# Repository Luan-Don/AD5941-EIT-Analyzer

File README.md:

# AD5941-EIT-Analyzer
This project is based on the previous project "AD5941 Impedance Analyzer" which extends further its application in Electrical Impedance Tomography. This project focuses on making the external PCB board (containing MUX) for AD5941 Impedance Analyzer (AIA for short).

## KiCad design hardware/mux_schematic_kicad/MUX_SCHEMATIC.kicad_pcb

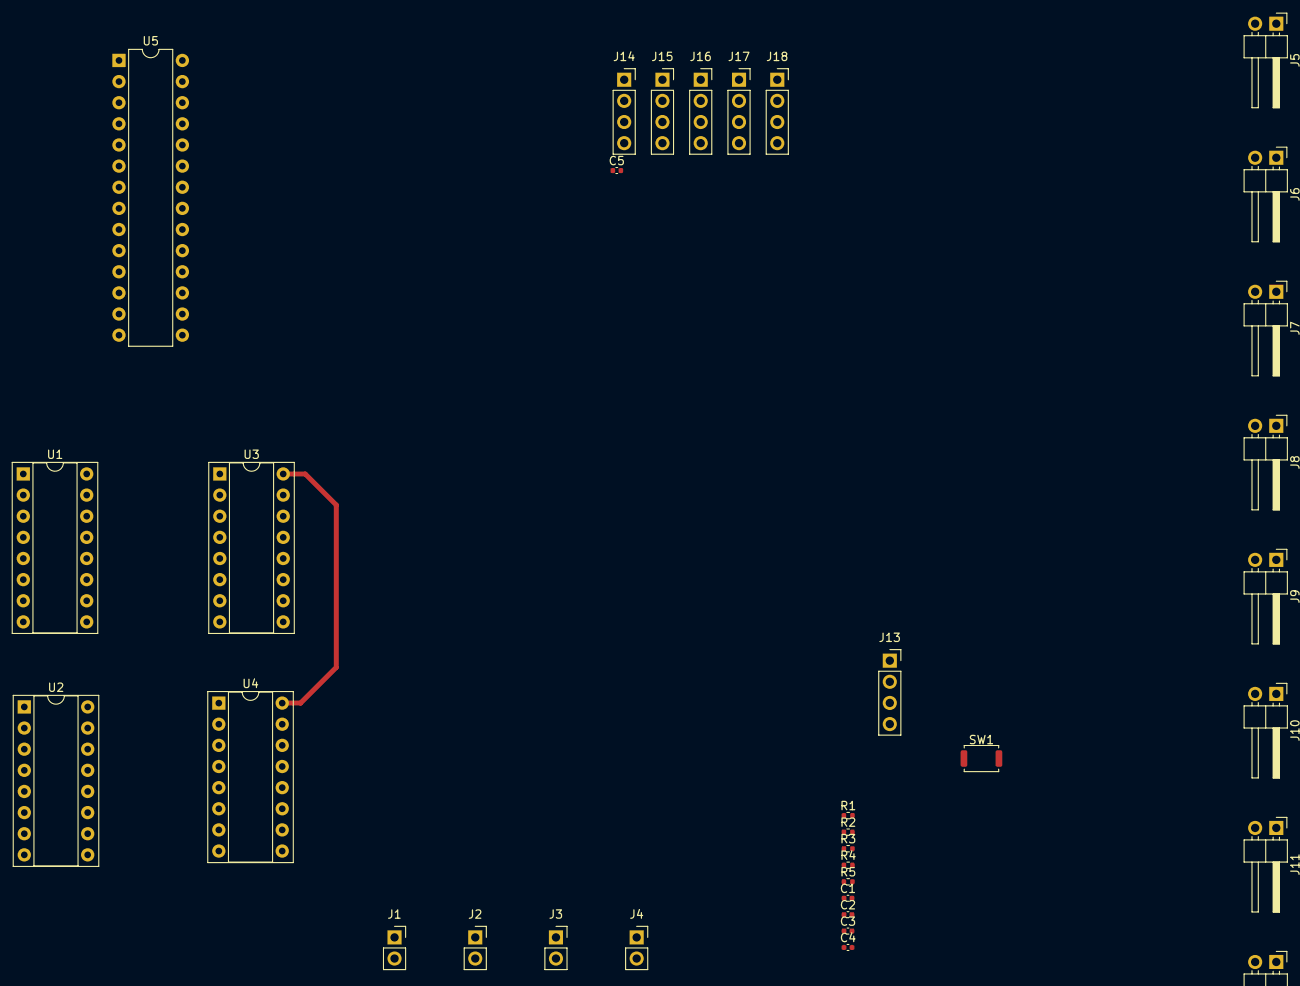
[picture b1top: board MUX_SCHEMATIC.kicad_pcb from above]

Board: 2 copper layers, 34 parts (0 on the bottom side), 37 nets.

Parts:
C1, C2, C3, C4, C5: 100n; C_0402_1005Metric
J1: CE0; PinSocket_1x02_P2.54mm_Vertical
J2: AIN1; PinSocket_1x02_P2.54mm_Vertical
J3: AIN2; PinSocket_1x02_P2.54mm_Vertical
J4: AIN3; PinSocket_1x02_P2.54mm_Vertical
J5: CNN1; PinHeader_1x02_P2.54mm_Horizontal
J6: CNN2; PinHeader_1x02_P2.54mm_Horizontal
J7: CNN3; PinHeader_1x02_P2.54mm_Horizontal
J8: CNN4; PinHeader_1x02_P2.54mm_Horizontal
J9: CNN5; PinHeader_1x02_P2.54mm_Horizontal
J10: CNN6; PinHeader_1x02_P2.54mm_Horizontal
J11: CNN7; PinHeader_1x02_P2.54mm_Horizontal
J12: CNN8; PinHeader_1x02_P2.54mm_Horizontal
J13: Conn_01x04; PinSocket_1x04_P2.54mm_Vertical
J14: MUX1_CON; PinSocket_1x04_P2.54mm_Vertical
J15: MUX2_CON; PinSocket_1x04_P2.54mm_Vertical
J16: MUX3_CON; PinSocket_1x04_P2.54mm_Vertical
J17: MUX4_CON; PinSocket_1x04_P2.54mm_Vertical
J18: MUX_COM; PinSocket_1x04_P2.54mm_Vertical
R1: 10k; R_0402_1005Metric
R2, R3, R4, R5: 1M; R_0402_1005Metric
SW1: RESET; SW_Push_SPST_NO_Alps_SKRK
U1, U2, U3, U4: 4051; DIP-16_W7.62mm_Socket
U5: MCP23017_SP; DIP-28_W7.62mm

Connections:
+3.3V: J13.4, R1.1, U1.16 (VDD), U2.16 (VDD), U3.16 (VDD), U4.16 (VDD), U5.9 (VDD)
/CNN1: J5.1 (In), U1.13 (X0), U2.13 (X0), U3.13 (X0), U4.13 (X0)
/CNN2: J6.1 (In), U1.14 (X1), U2.14 (X1), U3.14 (X1), U4.14 (X1)
/CNN3: J7.1 (In), U1.15 (X2), U2.15 (X2), U3.15 (X2), U4.15 (X2)
/CNN4: J8.1 (In), U1.12 (X3), U2.12 (X3), U3.12 (X3), U4.12 (X3)
/CNN5: J9.1 (In), U1.1 (X4), U2.1 (X4), U3.1 (X4), U4.1 (X4)
/CNN6: J10.1 (In), U1.5 (X5), U2.5 (X5), U3.5 (X5), U4.5 (X5)
/CNN7: J11.1 (In), U1.2 (X6), U2.2 (X6), U3.2 (X6), U4.2 (X6)
/CNN8: J12.1 (In), U1.4 (X7), U2.4 (X7), U3.4 (X7), U4.4 (X7)
/GPA0: J14.1, U1.6 (Inh), U5.21 (GPA0)
/GPA1: J14.2, U1.11 (A), U5.22 (GPA1)
/GPA2: J14.3, U1.10 (B), U5.23 (GPA2)
/GPA3: J14.4, U1.9 (C), U5.24 (GPA3)
/GPA4: J15.1, U2.6 (Inh), U5.25 (GPA4)
/GPA5: J15.2, U2.11 (A), U5.26 (GPA5)
/GPA6: J15.3, U2.10 (B), U5.27 (GPA6)
/GPA7: J15.4, U2.9 (C), U5.28 (GPA7)
/GPB0: J16.1, U3.6 (Inh), U5.1 (GPB0)
/GPB1: J16.2, U3.11 (A), U5.2 (GPB1)
/GPB2: J16.3, U3.10 (B), U5.3 (GPB2)
/GPB3: J16.4, U3.9 (C), U5.4 (GPB3)
/GPB4: J17.1, U4.6 (Inh), U5.5 (GPB4)
/GPB5: J17.2, U4.11 (A), U5.6 (GPB5)
/GPB6: J17.3, U4.10 (B), U5.7 (GPB6)
/GPB7: J17.4, U4.9 (C), U5.8 (GPB7)
/I2C1_SCL: J13.3, U5.12 (SCK)
/I2C1_SDA: J13.2, U5.13 (SDA)
/MUX1_COM: C1.2, J18.1, U1.3 (X)
/MUX2_COM: C2.2, J18.2, U2.3 (X)
/MUX3_COM: C3.2, J18.3, U3.3 (X)
/MUX4_COM: C4.2, J18.4, U4.3 (X)
GND: C5.1, J1.2 (Ext), J2.2 (Ext), J3.2 (Ext), J4.2 (Ext), J5.2 (Ext), J6.2 (Ext), J7.2 (Ext), J8.2 (Ext), J9.2 (Ext), J10.2 (Ext), J11.2 (Ext), J12.2 (Ext), J13.1, R2.2, R3.2, R4.2, R5.2, SW1.1, U1.7 (VEE), U1.8 (VSS), U2.7 (VEE), U2.8 (VSS), U3.7 (VEE), U3.8 (VSS), U4.7 (VEE), U4.8 (VSS), U5.10 (VSS), U5.15 (A0), U5.16 (A1), U5.17 (A2)
unnamed: C1.1, J1.1 (In), R2.1
unnamed: C2.1, J2.1 (In), R3.1
unnamed: C3.1, J3.1 (In), R4.1
unnamed: C4.1, J4.1 (In), R5.1
unnamed: C5.2, R1.2, SW1.2, U5.18 (~RESET)

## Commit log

2024-07-30 hw: add schematics, docs (8 channel, io expander)
2024-08-08 new signal diagram, new measuring pattern
2024-08-08 update weekly report - week 3
2024-08-09 update schematic with new design (v2.0)
2024-08-15 Ignore digital simulation
2024-09-03 update signal diagram
